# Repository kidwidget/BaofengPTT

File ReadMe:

First draft. PCB needs work.
Can use just about any logic level MOSFET.
This requires the Digikey library to be installed. 
https://forum.digikey.com/t/importing-the-digi-key-kicad-library-into-kicad-5-0-0/4075

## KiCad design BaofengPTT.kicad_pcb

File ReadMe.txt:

Work in progress
added DC block cap
Can use just about any logic level MOSFET.
This requires the Digikey library to be installed. 
https://forum.digikey.com/t/importing-the-digi-key-kicad-library-into-kicad-5-0-0/4075

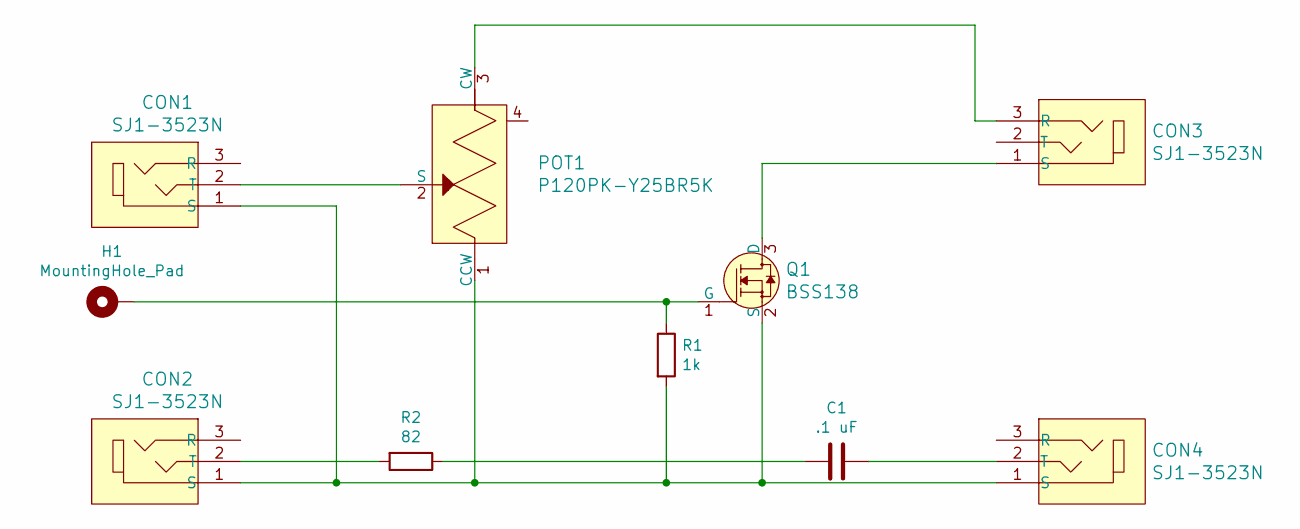
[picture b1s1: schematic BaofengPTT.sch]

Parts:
C1: .1 uF; C_Axial_L5.1mm_D3.1mm_P7.50mm_Horizontal
CON1, CON2, CON3, CON4: SJ1-3523N; Headphone_Jack_3.5mm_SJ1-3523N; MPN SJ1-3523N; Digi-Key_PN CP1-3523N-ND
H1: MountingHole_Pad; PinHeader_1x01_P2.54mm_Vertical
POT1: P120PK-Y25BR5K; Potentiometer_P120PK-Y25BR10K; MPN P120PK-Y25BR10K; Digi-Key_PN 987-1710-ND
Q1: BSS138; SOT-23-3; MPN BSS138; Digi-Key_PN BSS138CT-ND
R1: 1k; R_Axial_DIN0207_L6.3mm_D2.5mm_P7.62mm_Horizontal
R2: 82; R_Axial_DIN0207_L6.3mm_D2.5mm_P7.62mm_Horizontal

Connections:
unnamed: C1.1, CON4.2 (T)
unnamed: C1.2, R2.1
unnamed: CON1.1 (S), CON2.1 (S), CON4.1 (S), POT1.1 (CCW), Q1.2 (S), R1.2
unnamed: CON1.2 (T), POT1.2 (S)
unnamed: CON2.2 (T), R2.2
unnamed: CON3.1 (S), Q1.3 (D)
unnamed: CON3.3 (R), POT1.3 (CW)
unnamed: H1.1, Q1.1 (G), R1.1

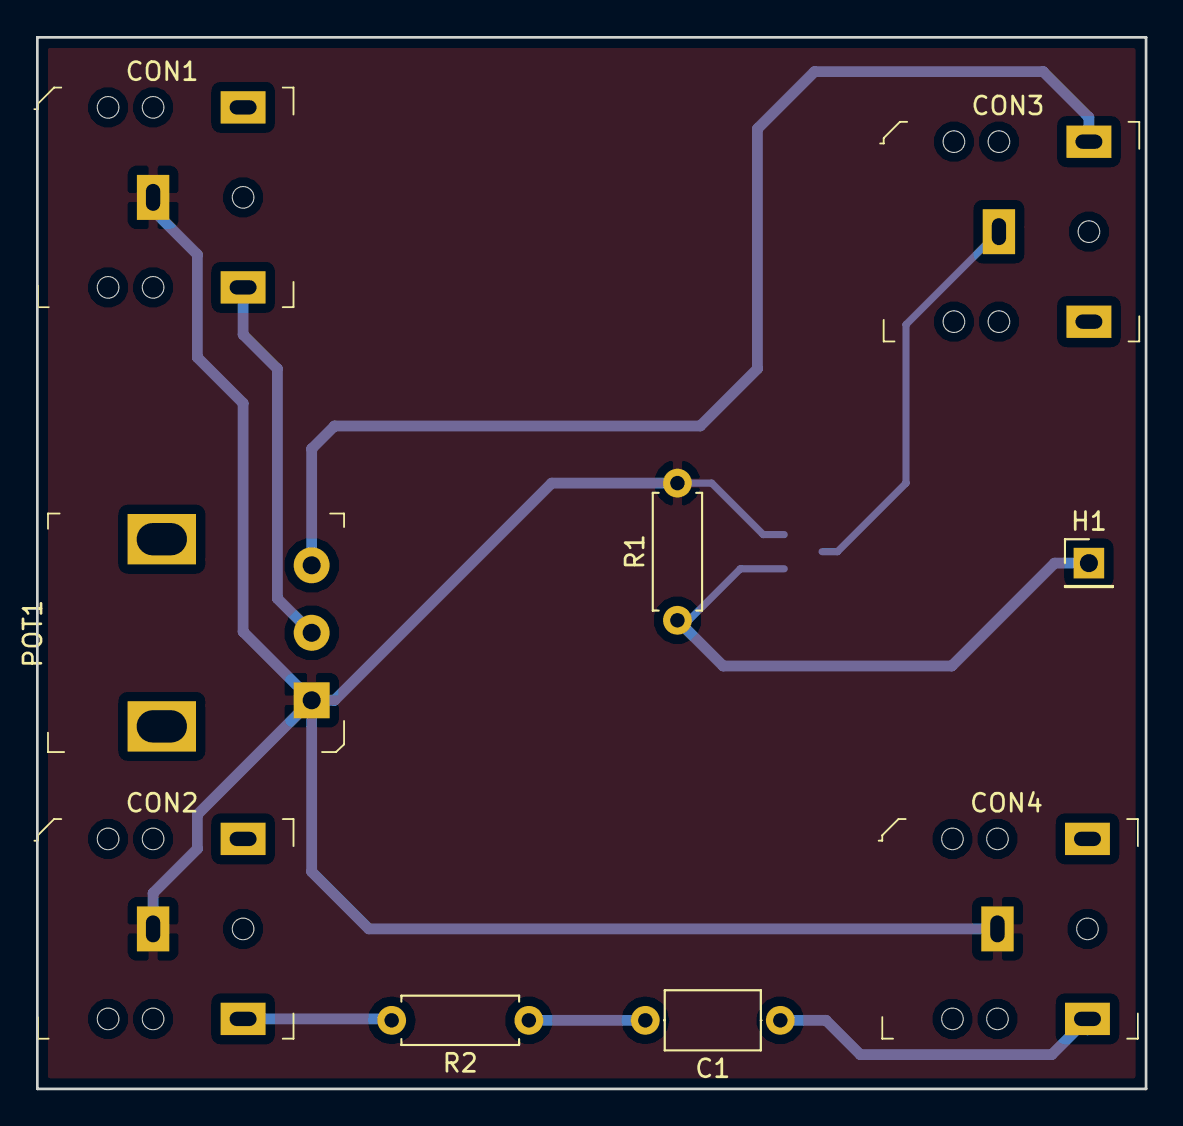
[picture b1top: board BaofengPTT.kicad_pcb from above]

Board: 2 copper layers, 61.6 x 58.4 mm, 10 parts (1 on the bottom side), 8 nets.

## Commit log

2020-08-07 added dc block capacitor
2020-08-08 added resitor to lower input level to sound card, placed top side coppor pour
2020-08-08 added notes to schematic
